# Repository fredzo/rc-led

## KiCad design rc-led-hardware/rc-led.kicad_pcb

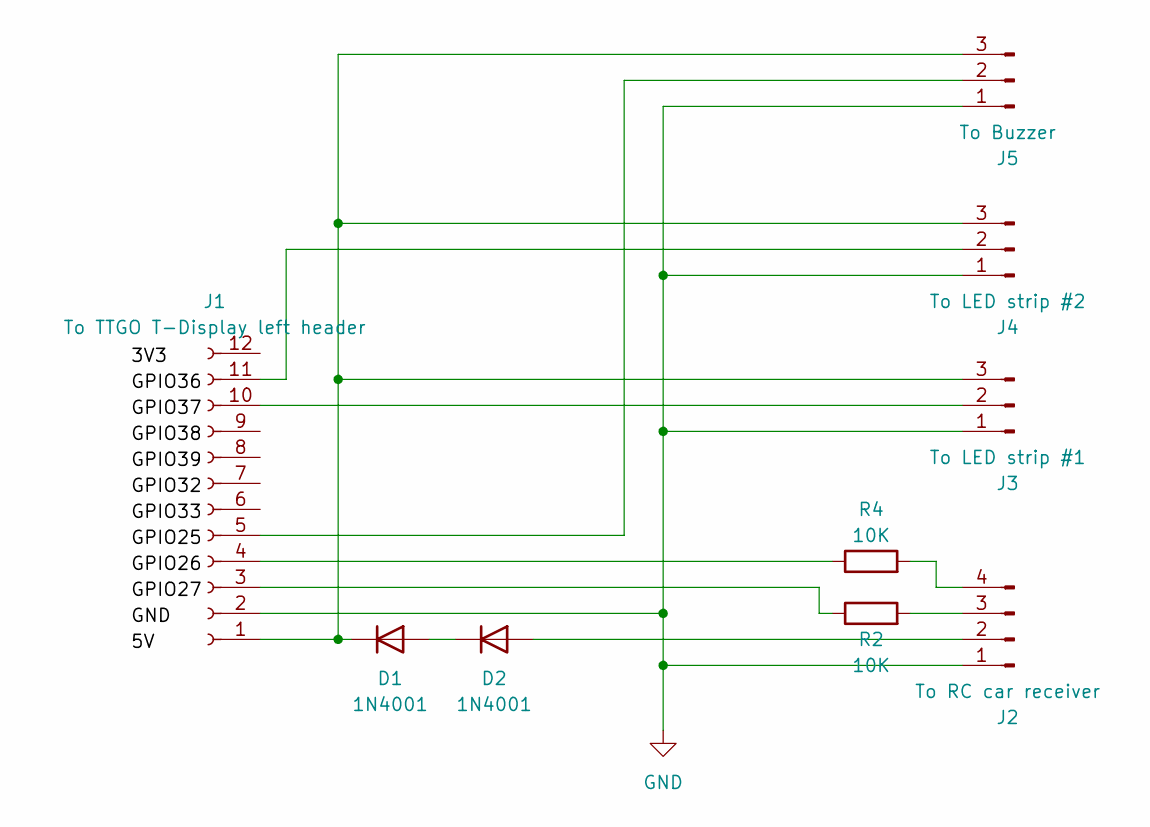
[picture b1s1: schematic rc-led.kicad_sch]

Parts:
D1, D2: 1N4001; D_DO-41_SOD81_P10.16mm_Horizontal
J1: To TTGO T-Display left header; PinHeader_1x12_P2.54mm_Vertical
J2: To RC car receiver; PinHeader_1x04_P2.54mm_Vertical
J3: To LED strip #1; PinHeader_1x03_P2.54mm_Vertical
J4: To LED strip #2; PinHeader_1x03_P2.54mm_Vertical
J5: To Buzzer; PinHeader_1x03_P2.54mm_Vertical
R2, R4: 10K; R_Axial_DIN0207_L6.3mm_D2.5mm_P7.62mm_Horizontal

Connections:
GND: J1.2, J2.1, J3.1, J4.1, J5.1
unnamed: D1.2 (A), D2.1 (K)
unnamed: D1.1 (K), J1.1, J3.3, J4.3, J5.3
unnamed: D2.2 (A), J2.2
unnamed: J1.3, R2.1
unnamed: J1.4, R4.1
unnamed: J1.5, J5.2
unnamed: J1.10, J3.2
unnamed: J1.11, J4.2
unnamed: J2.3, R2.2
unnamed: J2.4, R4.2

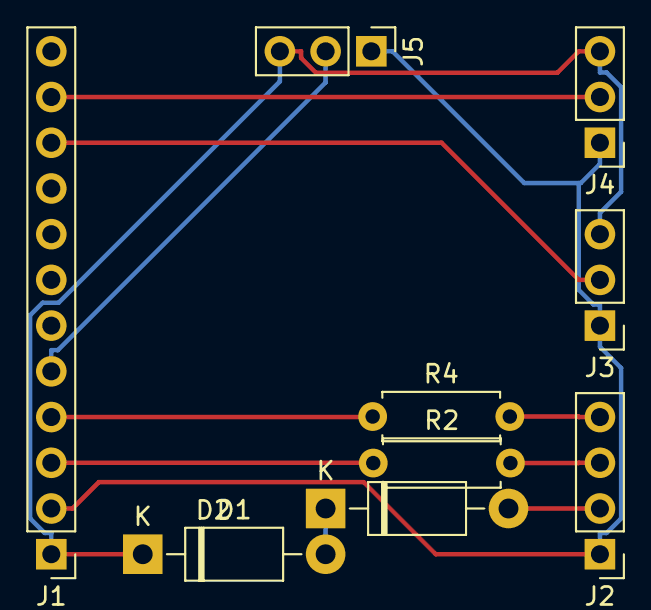
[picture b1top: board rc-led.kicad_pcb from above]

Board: 2 copper layers, 9 parts (0 on the bottom side), 11 nets.

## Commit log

2023-10-22 Blanc à l'allumage
2023-10-23 Plus de leds
2023-10-23 Ajout de define pour positions des leds
2023-10-26 Ajout du module EasyBuzzer
2023-10-26 Ajout du module EasyBuzzer. Ajout du deuxième bandeau led. Ajout des clignotants + fau de recul + buzzer + stop.
2023-10-26 Ajout de la sirène.
2023-10-26 Fix buzzer lib
2023-10-27 Fixed buzzer lib
2023-10-29 Nouvelle détection des positions de la télécommande avec pile des commandes. Détection du code Konami pour changement d'effets spéciaux. Ajout d'un effet terminator/cylon sur les yeux. Nettoyage des 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
2023-10-29 Désactivation debug
2023-10-30 Passage en mode interruption pour la détection du PWM des canaux radio.
2023-10-30 Correction de la détection du Knoami code. Correction de la durée du beep cligno (suite à l'accélération de la loop maintenant que la lecture PWM n'est plus blocante). Correction de la gestion des LE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
2023-10-30 Ajout des effest spéciaux gyro. Correction du deuxième cligno.
2023-10-31 Added schematics
2023-10-31 Refactoring LedManager
2023-11-01 Refacto EffectManager
2023-11-01 Radio module refacto + nommage leds en anglais
